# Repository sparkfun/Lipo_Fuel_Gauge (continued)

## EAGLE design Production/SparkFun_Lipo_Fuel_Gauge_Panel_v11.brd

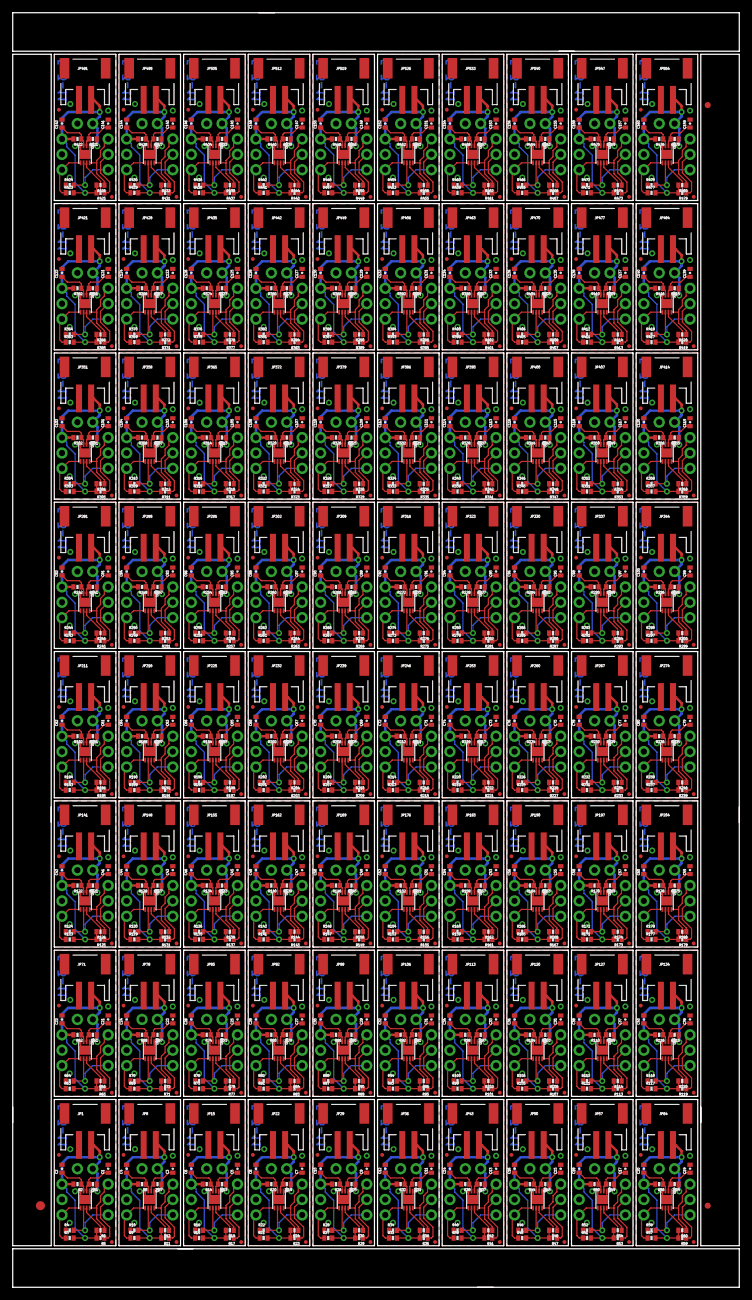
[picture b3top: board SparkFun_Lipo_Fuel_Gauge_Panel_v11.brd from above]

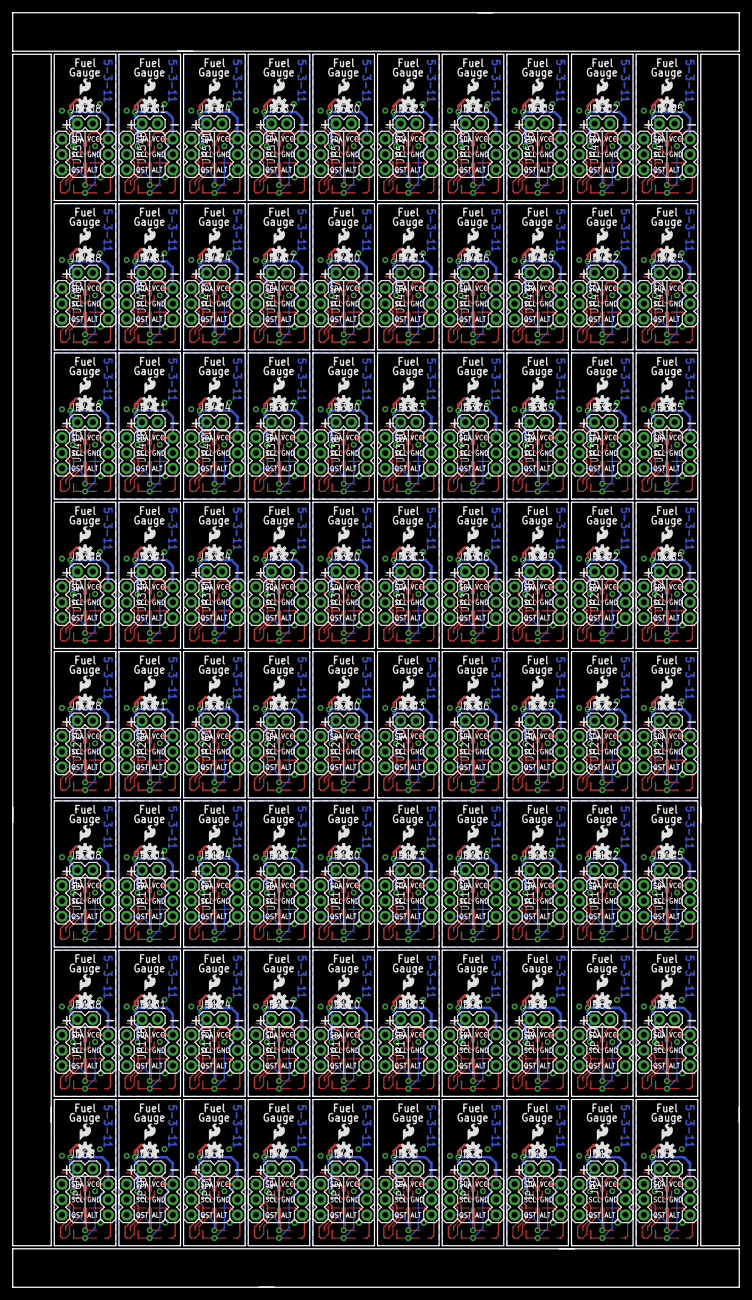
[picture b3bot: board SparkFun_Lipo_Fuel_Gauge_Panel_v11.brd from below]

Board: 2 copper layers, 119.9 x 210.3 mm, 1363 parts (400 on the bottom side), 640 nets.

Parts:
C1, C3, C5, C7, C9, C11, C13, C15, C17, C19, C21, C23, C25, C27, C29, C31, C33, C35, C37, C39, C41, C43, C45, C47, C49, C51, C53, C55, C57, C59, C61, C63, C65, C67, C69, C71, C73, C75, C77, C79, C81, C83, C85, C87, C89, C91, C93, C95, C97, C99, C101, C103, C105, C107, C109, C111, C113, C115, C117, C119, C121, C123, C125, C127, C129, C131, C133, C135, C137, C139, C141, C143, C145, C147, C149, C151, C153, C155, C157, C159: 1uF; 0402-CAP
C2, C4, C6, C8, C10, C12, C14, C16, C18, C20, C22, C24, C26, C28, C30, C32, C34, C36, C38, C40, C42, C44, C46, C48, C50, C52, C54, C56, C58, C60, C62, C64, C66, C68, C70, C72, C74, C76, C78, C80, C82, C84, C86, C88, C90, C92, C94, C96, C98, C100, C102, C104, C106, C108, C110, C112, C114, C116, C118, C120, C122, C124, C126, C128, C130, C132, C134, C136, C138, C140, C142, C144, C146, C148, C150, C152, C154, C156, C158, C160: 10nF; 0402-CAP
E$1: FIDUCIAL-1.5X3
E$2, E$5: FIDUCIAL-1X2
JP1, JP8, JP15, JP22, JP29, JP36, JP43, JP50, JP57, JP64, JP71, JP78, JP85, JP92, JP99, JP106, JP113, JP120, JP127, JP134, JP141, JP148, JP155, JP162, JP169, JP176, JP183, JP190, JP197, JP204, JP211, JP218, JP225, JP232, JP239, JP246, JP253, JP260, JP267, JP274, JP281, JP288, JP295, JP302, JP309, JP316, JP323, JP330, JP337, JP344, JP351, JP358, JP365, JP372, JP379, JP386, JP393, JP400, JP407, JP414, JP421, JP428, JP435, JP442, JP449, JP456, JP463, JP470, JP477, JP484, JP491, JP498, JP505, JP512, JP519, JP526, JP533, JP540, JP547, JP554: input; JST-2-SMD
JP2, JP4, JP9, JP10, JP16, JP17, JP23, JP24, JP30, JP31, JP37, JP38, JP44, JP45, JP51, JP52, JP58, JP59, JP65, JP66, JP72, JP73, JP79, JP80, JP86, JP87, JP93, JP94, JP100, JP101, JP107, JP108, JP114, JP115, JP121, JP122, JP128, JP129, JP135, JP136, JP142, JP143, JP149, JP150, JP156, JP157, JP163, JP164, JP170, JP171, JP177, JP178, JP184, JP185, JP191, JP192, JP198, JP199, JP205, JP206, JP212, JP213, JP219, JP220, JP226, JP227, JP233, JP234, JP240, JP241, JP247, JP248, JP254, JP255, JP261, JP262, JP268, JP269, JP275, JP276, JP282, JP283, JP289, JP290, JP296, JP297, JP303, JP304, JP310, JP311, JP317, JP318, JP324, JP325, JP331, JP332, JP338, JP339, JP345, JP346, JP352, JP353, JP359, JP360, JP366, JP367, JP373, JP374, JP380, JP381, JP387, JP388, JP394, JP395, JP401, JP402, JP408, JP409, JP415, JP416, JP422, JP423, JP429, JP430, JP436, JP437, JP443, JP444, JP450, JP451, JP457, JP458, JP464, JP465, JP471, JP472, JP478, JP479, JP485, JP486, JP492, JP493, JP499, JP500, JP506, JP507, JP513, JP514, JP520, JP521, JP527, JP528, JP534, JP535, JP541, JP542, JP548, JP549, JP555, JP556: 1X03
JP3, JP11, JP18, JP25, JP32, JP39, JP46, JP53, JP60, JP67, JP74, JP81, JP88, JP95, JP102, JP109, JP116, JP123, JP130, JP137, JP144, JP151, JP158, JP165, JP172, JP179, JP186, JP193, JP200, JP207, JP214, JP221, JP228, JP235, JP242, JP249, JP256, JP263, JP270, JP277, JP284, JP291, JP298, JP305, JP312, JP319, JP326, JP333, JP340, JP347, JP354, JP361, JP368, JP375, JP382, JP389, JP396, JP403, JP410, JP417, JP424, JP431, JP438, JP445, JP452, JP459, JP466, JP473, JP480, JP487, JP494, JP501, JP508, JP515, JP522, JP529, JP536, JP543, JP550, JP557: LOGO-SFESK; SFE-LOGO-FLAME
JP5, JP12, JP19, JP26, JP33, JP40, JP47, JP54, JP61, JP68, JP75, JP82, JP89, JP96, JP103, JP110, JP117, JP124, JP131, JP138, JP145, JP152, JP159, JP166, JP173, JP180, JP187, JP194, JP201, JP208, JP215, JP222, JP229, JP236, JP243, JP250, JP257, JP264, JP271, JP278, JP285, JP292, JP299, JP306, JP313, JP320, JP327, JP334, JP341, JP348, JP355, JP362, JP369, JP376, JP383, JP390, JP397, JP404, JP411, JP418, JP425, JP432, JP439, JP446, JP453, JP460, JP467, JP474, JP481, JP488, JP495, JP502, JP509, JP516, JP523, JP530, JP537, JP544, JP551, JP558: 1X02
JP6, JP7, JP13, JP14, JP20, JP21, JP27, JP28, JP34, JP35, JP41, JP42, JP48, JP49, JP55, JP56, JP62, JP63, JP69, JP70, JP76, JP77, JP83, JP84, JP90, JP91, JP97, JP98, JP104, JP105, JP111, JP112, JP118, JP119, JP125, JP126, JP132, JP133, JP139, JP140, JP146, JP147, JP153, JP154, JP160, JP161, JP167, JP168, JP174, JP175, JP181, JP182, JP188, JP189, JP195, JP196, JP202, JP203, JP209, JP210, JP216, JP217, JP223, JP224, JP230, JP231, JP237, JP238, JP244, JP245, JP251, JP252, JP258, JP259, JP265, JP266, JP272, JP273, JP279, JP280, JP286, JP287, JP293, JP294, JP300, JP301, JP307, JP308, JP314, JP315, JP321, JP322, JP328, JP329, JP335, JP336, JP342, JP343, JP349, JP350, JP356, JP357, JP363, JP364, JP370, JP371, JP377, JP378, JP384, JP385, JP391, JP392, JP398, JP399, JP405, JP406, JP412, JP413, JP419, JP420, JP426, JP427, JP433, JP434, JP440, JP441, JP447, JP448, JP454, JP455, JP461, JP462, JP468, JP469, JP475, JP476, JP482, JP483, JP489, JP490, JP496, JP497, JP503, JP504, JP510, JP511, JP517, JP518, JP524, JP525, JP531, JP532, JP538, JP539, JP545, JP546, JP552, JP553, JP559, JP560: FIDUCIAL1X2.5; FIDUCIAL-1X2.5
R1, R7, R13, R19, R25, R31, R37, R43, R49, R55, R61, R67, R73, R79, R85, R91, R97, R103, R109, R115, R121, R127, R133, R139, R145, R151, R157, R163, R169, R175, R181, R187, R193, R199, R205, R211, R217, R223, R229, R235, R241, R247, R253, R259, R265, R271, R277, R283, R289, R295, R301, R307, R313, R319, R325, R331, R337, R343, R349, R355, R361, R367, R373, R379, R385, R391, R397, R403, R409, R415, R421, R427, R433, R439, R445, R451, R457, R463, R469, R475: 1k; 0402-RES
R2, R8, R14, R20, R26, R32, R38, R44, R50, R56, R62, R68, R74, R80, R86, R92, R98, R104, R110, R116, R122, R128, R134, R140, R146, R152, R158, R164, R170, R176, R182, R188, R194, R200, R206, R212, R218, R224, R230, R236, R242, R248, R254, R260, R266, R272, R278, R284, R290, R296, R302, R308, R314, R320, R326, R332, R338, R344, R350, R356, R362, R368, R374, R380, R386, R392, R398, R404, R410, R416, R422, R428, R434, R440, R446, R452, R458, R464, R470, R476: 180; 0402-RES
R3, R4, R5, R6, R9, R10, R11, R12, R15, R16, R17, R18, R21, R22, R23, R24, R27, R28, R29, R30, R33, R34, R35, R36, R39, R40, R41, R42, R45, R46, R47, R48, R51, R52, R53, R54, R57, R58, R59, R60, R63, R64, R65, R66, R69, R70, R71, R72, R75, R76, R77, R78, R81, R82, R83, R84, R87, R88, R89, R90, R93, R94, R95, R96, R99, R100, R101, R102, R105, R106, R107, R108, R111, R112, R113, R114, R117, R118, R119, R120, R123, R124, R125, R126, R129, R130, R131, R132, R135, R136, R137, R138, R141, R142, R143, R144, R147, R148, R149, R150, R153, R154, R155, R156, R159, R160, R161, R162, R165, R166, R167, R168, R171, R172, R173, R174, R177, R178, R179, R180, R183, R184, R185, R186, R189, R190, R191, R192, R195, R196, R197, R198, R201, R202, R203, R204, R207, R208, R209, R210, R213, R214, R215, R216, R219, R220, R221, R222, R225, R226, R227, R228, R231, R232, R233, R234, R237, R238, R239, R240, R243, R244, R245, R246, R249, R250, R251, R252, R255, R256, R257, R258, R261, R262, R263, R264, R267, R268, R269, R270, R273, R274, R275, R276, R279, R280, R281, R282, R285, R286, R287, R288, R291, R292, R293, R294, R297, R298, R299, R300, R303, R304, R305, R306, R309, R310, R311, R312, R315, R316, R317, R318, R321, R322, R323, R324, R327, R328, R329, R330, R333, R334, R335, R336, R339, R340, R341, R342, R345, R346, R347, R348, R351, R352, R353, R354, R357, R358, R359, R360, R363, R364, R365, R366, R369, R370, R371, R372, R375, R376, R377, R378, R381, R382, R383, R384, R387, R388, R389, R390, R393, R394, R395, R396, R399, R400, R401, R402, R405, R406, R407, R408, R411, R412, R413, R414, R417, R418, R419, R420, R423, R424, R425, R426, R429, R430, R431, R432, R435, R436, R437, R438, R441, R442, R443, R444, R447, R448, R449, R450, R453, R454, R455, R456, R459, R460, R461, R462, R465, R466, R467, R468, R471, R472, R473, R474, R477, R478, R479, R480: 4.7k; 0402-RES
U1, U2, U3, U4, U5, U6, U7, U8, U9, U10, U11, U12, U13, U14, U15, U16, U17, U18, U19, U20, U21, U22, U23, U24, U25, U26, U27, U28, U29, U30, U31, U32, U33, U34, U35, U36, U37, U38, U39, U40, U41, U42, U43, U44, U45, U46, U47, U48, U49, U50, U51, U52, U53, U54, U55, U56, U57, U58, U59, U60, U61, U62, U63, U64, U65, U66, U67, U68, U69, U70, U71, U72, U73, U74, U75, U76, U77, U78, U79, U80: MAX1704X; TDFN-8
U$1, U$2, U$3, U$4, U$5, U$6, U$7, U$8, U$9, U$10, U$11, U$12, U$13, U$14, U$15, U$16, U$17, U$18, U$19, U$20, U$21, U$22, U$23, U$24, U$25, U$26, U$27, U$28, U$29, U$30, U$31, U$32, U$33, U$34, U$35, U$36, U$37, U$38, U$39, U$40, U$41, U$42, U$43, U$44, U$45, U$46, U$47, U$48, U$49, U$50, U$51, U$52, U$53, U$54, U$55, U$56, U$57, U$58, U$59, U$60, U$61, U$62, U$63, U$64, U$65, U$66, U$67, U$68, U$69, U$70, U$71, U$72, U$73, U$74, U$75, U$76, U$77, U$78, U$79, U$80: OSHW-LOGOS; OSHW-LOGO-S

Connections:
ALT: JP4.3, R3.1, U2.5
ALT1: JP10.3, R9.1, U1.5
ALT2: JP17.3, R15.1, U3.5
ALT3: JP24.3, R21.1, U4.5
ALT4: JP31.3, R27.1, U5.5
ALT5: JP38.3, R33.1, U6.5
ALT6: JP45.3, R39.1, U7.5
ALT7: JP52.3, R45.1, U8.5
ALT8: JP59.3, R51.1, U9.5
ALT9: JP66.3, R57.1, U10.5
ALT10: JP73.3, R63.1, U11.5
ALT11: JP80.3, R69.1, U12.5
ALT12: JP87.3, R75.1, U13.5
ALT13: JP94.3, R81.1, U14.5
ALT14: JP101.3, R87.1, U15.5
ALT15: JP108.3, R93.1, U16.5
ALT16: JP115.3, R99.1, U17.5
ALT17: JP122.3, R105.1, U18.5
ALT18: JP129.3, R111.1, U19.5
ALT19: JP136.3, R117.1, U20.5
ALT20: JP143.3, R123.1, U21.5
ALT21: JP150.3, R129.1, U22.5
ALT22: JP157.3, R135.1, U23.5
ALT23: JP164.3, R141.1, U24.5
ALT24: JP171.3, R147.1, U25.5
ALT25: JP178.3, R153.1, U26.5
ALT26: JP185.3, R159.1, U27.5
ALT27: JP192.3, R165.1, U28.5
ALT28: JP199.3, R171.1, U29.5
ALT29: JP206.3, R177.1, U30.5
ALT30: JP213.3, R183.1, U31.5
ALT31: JP220.3, R189.1, U32.5
ALT32: JP227.3, R195.1, U33.5
ALT33: JP234.3, R201.1, U34.5
ALT34: JP241.3, R207.1, U35.5
ALT35: JP248.3, R213.1, U36.5
ALT36: JP255.3, R219.1, U37.5
ALT37: JP262.3, R225.1, U38.5
ALT38: JP269.3, R231.1, U39.5
ALT39: JP276.3, R237.1, U40.5
ALT40: JP283.3, R243.1, U41.5
ALT41: JP290.3, R249.1, U42.5
ALT42: JP297.3, R255.1, U43.5
ALT43: JP304.3, R261.1, U44.5
ALT44: JP311.3, R267.1, U45.5
ALT45: JP318.3, R273.1, U46.5
ALT46: JP325.3, R279.1, U47.5
ALT47: JP332.3, R285.1, U48.5
ALT48: JP339.3, R291.1, U49.5
ALT49: JP346.3, R297.1, U50.5
ALT50: JP353.3, R303.1, U51.5
ALT51: JP360.3, R309.1, U52.5
ALT52: JP367.3, R315.1, U53.5
ALT53: JP374.3, R321.1, U54.5
ALT54: JP381.3, R327.1, U55.5
ALT55: JP388.3, R333.1, U56.5
ALT56: JP395.3, R339.1, U57.5
ALT57: JP402.3, R345.1, U58.5
ALT58: JP409.3, R351.1, U59.5
ALT59: JP416.3, R357.1, U60.5
ALT60: JP423.3, R363.1, U61.5
ALT61: JP430.3, R369.1, U62.5
ALT62: JP437.3, R375.1, U63.5
ALT63: JP444.3, R381.1, U64.5
ALT64: JP451.3, R387.1, U65.5
ALT65: JP458.3, R393.1, U66.5
ALT66: JP465.3, R399.1, U67.5
ALT67: JP472.3, R405.1, U68.5
ALT68: JP479.3, R411.1, U69.5
ALT69: JP486.3, R417.1, U70.5
ALT70: JP493.3, R423.1, U71.5
ALT71: JP500.3, R429.1, U72.5
ALT72: JP507.3, R435.1, U73.5
ALT73: JP514.3, R441.1, U74.5
ALT74: JP521.3, R447.1, U75.5
ALT75: JP528.3, R453.1, U76.5
ALT76: JP535.3, R459.1, U77.5
ALT77: JP542.3, R465.1, U78.5
ALT78: JP549.3, R471.1, U79.5
ALT79: JP556.3, R477.1, U80.5
GND: C1.2, C2.2, JP1.1, JP4.2, JP5.2, R4.1, U2.1, U2.4, U2.EP
GND1: C3.2, C4.2, JP8.1, JP10.2, JP12.2, R10.1, U1.1, U1.4, U1.EP
GND2: C5.2, C6.2, JP15.1, JP17.2, JP19.2, R16.1, U3.1, U3.4, U3.EP
GND3: C7.2, C8.2, JP22.1, JP24.2, JP26.2, R22.1, U4.1, U4.4, U4.EP
GND4: C9.2, C10.2, JP29.1, JP31.2, JP33.2, R28.1, U5.1, U5.4, U5.EP
GND5: C11.2, C12.2, JP36.1, JP38.2, JP40.2, R34.1, U6.1, U6.4, U6.EP
GND6: C13.2, C14.2, JP43.1, JP45.2, JP47.2, R40.1, U7.1, U7.4, U7.EP
GND7: C15.2, C16.2, JP50.1, JP52.2, JP54.2, R46.1, U8.1, U8.4, U8.EP
GND8: C17.2, C18.2, JP57.1, JP59.2, JP61.2, R52.1, U9.1, U9.4, U9.EP
GND9: C19.2, C20.2, JP64.1, JP66.2, JP68.2, R58.1, U10.1, U10.4, U10.EP
GND10: C21.2, C22.2, JP71.1, JP73.2, JP75.2, R64.1, U11.1, U11.4, U11.EP
GND11: C23.2, C24.2, JP78.1, JP80.2, JP82.2, R70.1, U12.1, U12.4, U12.EP
GND12: C25.2, C26.2, JP85.1, JP87.2, JP89.2, R76.1, U13.1, U13.4, U13.EP
GND13: C27.2, C28.2, JP92.1, JP94.2, JP96.2, R82.1, U14.1, U14.4, U14.EP
GND14: C29.2, C30.2, JP99.1, JP101.2, JP103.2, R88.1, U15.1, U15.4, U15.EP
GND15: C31.2, C32.2, JP106.1, JP108.2, JP110.2, R94.1, U16.1, U16.4, U16.EP
GND16: C33.2, C34.2, JP113.1, JP115.2, JP117.2, R100.1, U17.1, U17.4, U17.EP
GND17: C35.2, C36.2, JP120.1, JP122.2, JP124.2, R106.1, U18.1, U18.4, U18.EP
GND18: C37.2, C38.2, JP127.1, JP129.2, JP131.2, R112.1, U19.1, U19.4, U19.EP
GND19: C39.2, C40.2, JP134.1, JP136.2, JP138.2, R118.1, U20.1, U20.4, U20.EP
GND20: C41.2, C42.2, JP141.1, JP143.2, JP145.2, R124.1, U21.1, U21.4, U21.EP
GND21: C43.2, C44.2, JP148.1, JP150.2, JP152.2, R130.1, U22.1, U22.4, U22.EP
GND22: C45.2, C46.2, JP155.1, JP157.2, JP159.2, R136.1, U23.1, U23.4, U23.EP
GND23: C47.2, C48.2, JP162.1, JP164.2, JP166.2, R142.1, U24.1, U24.4, U24.EP
GND24: C49.2, C50.2, JP169.1, JP171.2, JP173.2, R148.1, U25.1, U25.4, U25.EP
GND25: C51.2, C52.2, JP176.1, JP178.2, JP180.2, R154.1, U26.1, U26.4, U26.EP
GND26: C53.2, C54.2, JP183.1, JP185.2, JP187.2, R160.1, U27.1, U27.4, U27.EP
GND27: C55.2, C56.2, JP190.1, JP192.2, JP194.2, R166.1, U28.1, U28.4, U28.EP
GND28: C57.2, C58.2, JP197.1, JP199.2, JP201.2, R172.1, U29.1, U29.4, U29.EP
GND29: C59.2, C60.2, JP204.1, JP206.2, JP208.2, R178.1, U30.1, U30.4, U30.EP
GND30: C61.2, C62.2, JP211.1, JP213.2, JP215.2, R184.1, U31.1, U31.4, U31.EP
GND31: C63.2, C64.2, JP218.1, JP220.2, JP222.2, R190.1, U32.1, U32.4, U32.EP
GND32: C65.2, C66.2, JP225.1, JP227.2, JP229.2, R196.1, U33.1, U33.4, U33.EP
GND33: C67.2, C68.2, JP232.1, JP234.2, JP236.2, R202.1, U34.1, U34.4, U34.EP
GND34: C69.2, C70.2, JP239.1, JP241.2, JP243.2, R208.1, U35.1, U35.4, U35.EP
GND35: C71.2, C72.2, JP246.1, JP248.2, JP250.2, R214.1, U36.1, U36.4, U36.EP
GND36: C73.2, C74.2, JP253.1, JP255.2, JP257.2, R220.1, U37.1, U37.4, U37.EP
GND37: C75.2, C76.2, JP260.1, JP262.2, JP264.2, R226.1, U38.1, U38.4, U38.EP
GND38: C77.2, C78.2, JP267.1, JP269.2, JP271.2, R232.1, U39.1, U39.4, U39.EP
GND39: C79.2, C80.2, JP274.1, JP276.2, JP278.2, R238.1, U40.1, U40.4, U40.EP
GND40: C81.2, C82.2, JP281.1, JP283.2, JP285.2, R244.1, U41.1, U41.4, U41.EP
GND41: C83.2, C84.2, JP288.1, JP290.2, JP292.2, R250.1, U42.1, U42.4, U42.EP
GND42: C85.2, C86.2, JP295.1, JP297.2, JP299.2, R256.1, U43.1, U43.4, U43.EP
GND43: C87.2, C88.2, JP302.1, JP304.2, JP306.2, R262.1, U44.1, U44.4, U44.EP
GND44: C89.2, C90.2, JP309.1, JP311.2, JP313.2, R268.1, U45.1, U45.4, U45.EP
GND45: C91.2, C92.2, JP316.1, JP318.2, JP320.2, R274.1, U46.1, U46.4, U46.EP
GND46: C93.2, C94.2, JP323.1, JP325.2, JP327.2, R280.1, U47.1, U47.4, U47.EP
GND47: C95.2, C96.2, JP330.1, JP332.2, JP334.2, R286.1, U48.1, U48.4, U48.EP
GND48: C97.2, C98.2, JP337.1, JP339.2, JP341.2, R292.1, U49.1, U49.4, U49.EP
GND49: C99.2, C100.2, JP344.1, JP346.2, JP348.2, R298.1, U50.1, U50.4, U50.EP
GND50: C101.2, C102.2, JP351.1, JP353.2, JP355.2, R304.1, U51.1, U51.4, U51.EP
GND51: C103.2, C104.2, JP358.1, JP360.2, JP362.2, R310.1, U52.1, U52.4, U52.EP
GND52: C105.2, C106.2, JP365.1, JP367.2, JP369.2, R316.1, U53.1, U53.4, U53.EP
GND53: C107.2, C108.2, JP372.1, JP374.2, JP376.2, R322.1, U54.1, U54.4, U54.EP
GND54: C109.2, C110.2, JP379.1, JP381.2, JP383.2, R328.1, U55.1, U55.4, U55.EP
GND55: C111.2, C112.2, JP386.1, JP388.2, JP390.2, R334.1, U56.1, U56.4, U56.EP
GND56: C113.2, C114.2, JP393.1, JP395.2, JP397.2, R340.1, U57.1, U57.4, U57.EP
GND57: C115.2, C116.2, JP400.1, JP402.2, JP404.2, R346.1, U58.1, U58.4, U58.EP
GND58: C117.2, C118.2, JP407.1, JP409.2, JP411.2, R352.1, U59.1, U59.4, U59.EP
GND59: C119.2, C120.2, JP414.1, JP416.2, JP418.2, R358.1, U60.1, U60.4, U60.EP
GND60: C121.2, C122.2, JP421.1, JP423.2, JP425.2, R364.1, U61.1, U61.4, U61.EP
GND61: C123.2, C124.2, JP428.1, JP430.2, JP432.2, R370.1, U62.1, U62.4, U62.EP
GND62: C125.2, C126.2, JP435.1, JP437.2, JP439.2, R376.1, U63.1, U63.4, U63.EP
GND63: C127.2, C128.2, JP442.1, JP444.2, JP446.2, R382.1, U64.1, U64.4, U64.EP
GND64: C129.2, C130.2, JP449.1, JP451.2, JP453.2, R388.1, U65.1, U65.4, U65.EP
GND65: C131.2, C132.2, JP456.1, JP458.2, JP460.2, R394.1, U66.1, U66.4, U66.EP
GND66: C133.2, C134.2, JP463.1, JP465.2, JP467.2, R400.1, U67.1, U67.4, U67.EP
GND67: C135.2, C136.2, JP470.1, JP472.2, JP474.2, R406.1, U68.1, U68.4, U68.EP
GND68: C137.2, C138.2, JP477.1, JP479.2, JP481.2, R412.1, U69.1, U69.4, U69.EP
GND69: C139.2, C140.2, JP484.1, JP486.2, JP488.2, R418.1, U70.1, U70.4, U70.EP
GND70: C141.2, C142.2, JP491.1, JP493.2, JP495.2, R424.1, U71.1, U71.4, U71.EP
GND71: C143.2, C144.2, JP498.1, JP500.2, JP502.2, R430.1, U72.1, U72.4, U72.EP
GND72: C145.2, C146.2, JP505.1, JP507.2, JP509.2, R436.1, U73.1, U73.4, U73.EP
GND73: C147.2, C148.2, JP512.1, JP514.2, JP516.2, R442.1, U74.1, U74.4, U74.EP
GND74: C149.2, C150.2, JP519.1, JP521.2, JP523.2, R448.1, U75.1, U75.4, U75.EP
GND75: C151.2, C152.2, JP526.1, JP528.2, JP530.2, R454.1, U76.1, U76.4, U76.EP
GND76: C153.2, C154.2, JP533.1, JP535.2, JP537.2, R460.1, U77.1, U77.4, U77.EP
GND77: C155.2, C156.2, JP540.1, JP542.2, JP544.2, R466.1, U78.1, U78.4, U78.EP
GND78: C157.2, C158.2, JP547.1, JP549.2, JP551.2, R472.1, U79.1, U79.4, U79.EP
GND79: C159.2, C160.2, JP554.1, JP556.2, JP558.2, R478.1, U80.1, U80.4, U80.EP
unnamed: C3.1, R7.2, U1.2
unnamed: C1.1, R1.2, U2.2
unnamed: C5.1, R13.2, U3.2
unnamed: C7.1, R19.2, U4.2
unnamed: C9.1, R25.2, U5.2
unnamed: C11.1, R31.2, U6.2
unnamed: C13.1, R37.2, U7.2
unnamed: C15.1, R43.2, U8.2
unnamed: C17.1, R49.2, U9.2
unnamed: C19.1, R55.2, U10.2
unnamed: C21.1, R61.2, U11.2
unnamed: C23.1, R67.2, U12.2
unnamed: C25.1, R73.2, U13.2
unnamed: C27.1, R79.2, U14.2
unnamed: C29.1, R85.2, U15.2
unnamed: C31.1, R91.2, U16.2
unnamed: C33.1, R97.2, U17.2
unnamed: C35.1, R103.2, U18.2
unnamed: C37.1, R109.2, U19.2
unnamed: C39.1, R115.2, U20.2
unnamed: C41.1, R121.2, U21.2
unnamed: C43.1, R127.2, U22.2
unnamed: C45.1, R133.2, U23.2
unnamed: C47.1, R139.2, U24.2
unnamed: C49.1, R145.2, U25.2
unnamed: C51.1, R151.2, U26.2
unnamed: C53.1, R157.2, U27.2
unnamed: C55.1, R163.2, U28.2
unnamed: C57.1, R169.2, U29.2
unnamed: C59.1, R175.2, U30.2
unnamed: C61.1, R181.2, U31.2
unnamed: C63.1, R187.2, U32.2
unnamed: C65.1, R193.2, U33.2
unnamed: C67.1, R199.2, U34.2
unnamed: C69.1, R205.2, U35.2
unnamed: C71.1, R211.2, U36.2
unnamed: C73.1, R217.2, U37.2
unnamed: C75.1, R223.2, U38.2
unnamed: C77.1, R229.2, U39.2
unnamed: C79.1, R235.2, U40.2
unnamed: C81.1, R241.2, U41.2
unnamed: C83.1, R247.2, U42.2
unnamed: C85.1, R253.2, U43.2
unnamed: C87.1, R259.2, U44.2
unnamed: C89.1, R265.2, U45.2
unnamed: C91.1, R271.2, U46.2
unnamed: C93.1, R277.2, U47.2
unnamed: C95.1, R283.2, U48.2
unnamed: C97.1, R289.2, U49.2
unnamed: C99.1, R295.2, U50.2
unnamed: C101.1, R301.2, U51.2
unnamed: C103.1, R307.2, U52.2
unnamed: C105.1, R313.2, U53.2
unnamed: C107.1, R319.2, U54.2
unnamed: C109.1, R325.2, U55.2
unnamed: C111.1, R331.2, U56.2
unnamed: C113.1, R337.2, U57.2
unnamed: C115.1, R343.2, U58.2
unnamed: C117.1, R349.2, U59.2
unnamed: C119.1, R355.2, U60.2
unnamed: C121.1, R361.2, U61.2
unnamed: C123.1, R367.2, U62.2
unnamed: C125.1, R373.2, U63.2
unnamed: C127.1, R379.2, U64.2
unnamed: C129.1, R385.2, U65.2
unnamed: C131.1, R391.2, U66.2
unnamed: C133.1, R397.2, U67.2
unnamed: C135.1, R403.2, U68.2
unnamed: C137.1, R409.2, U69.2
unnamed: C139.1, R415.2, U70.2
unnamed: C141.1, R421.2, U71.2
unnamed: C143.1, R427.2, U72.2
unnamed: C145.1, R433.2, U73.2
unnamed: C147.1, R439.2, U74.2
unnamed: C149.1, R445.2, U75.2
unnamed: C151.1, R451.2, U76.2
unnamed: C153.1, R457.2, U77.2
unnamed: C155.1, R463.2, U78.2
unnamed: C157.1, R469.2, U79.2
unnamed: C159.1, R475.2, U80.2
QST: JP2.3, R4.2, U2.6
QST1: JP9.3, R10.2, U1.6
QST2: JP16.3, R16.2, U3.6
QST3: JP23.3, R22.2, U4.6
QST4: JP30.3, R28.2, U5.6
QST5: JP37.3, R34.2, U6.6
QST6: JP44.3, R40.2, U7.6
QST7: JP51.3, R46.2, U8.6
QST8: JP58.3, R52.2, U9.6
QST9: JP65.3, R58.2, U10.6
QST10: JP72.3, R64.2, U11.6
QST11: JP79.3, R70.2, U12.6
QST12: JP86.3, R76.2, U13.6
QST13: JP93.3, R82.2, U14.6
QST14: JP100.3, R88.2, U15.6
QST15: JP107.3, R94.2, U16.6
QST16: JP114.3, R100.2, U17.6
QST17: JP121.3, R106.2, U18.6
QST18: JP128.3, R112.2, U19.6
QST19: JP135.3, R118.2, U20.6
QST20: JP142.3, R124.2, U21.6
QST21: JP149.3, R130.2, U22.6
QST22: JP156.3, R136.2, U23.6
QST23: JP163.3, R142.2, U24.6
QST24: JP170.3, R148.2, U25.6
QST25: JP177.3, R154.2, U26.6
QST26: JP184.3, R160.2, U27.6
QST27: JP191.3, R166.2, U28.6
QST28: JP198.3, R172.2, U29.6
QST29: JP205.3, R178.2, U30.6
QST30: JP212.3, R184.2, U31.6
QST31: JP219.3, R190.2, U32.6
QST32: JP226.3, R196.2, U33.6
QST33: JP233.3, R202.2, U34.6
QST34: JP240.3, R208.2, U35.6
QST35: JP247.3, R214.2, U36.6
QST36: JP254.3, R220.2, U37.6
QST37: JP261.3, R226.2, U38.6
QST38: JP268.3, R232.2, U39.6
QST39: JP275.3, R238.2, U40.6
QST40: JP282.3, R244.2, U41.6
QST41: JP289.3, R250.2, U42.6
QST42: JP296.3, R256.2, U43.6
QST43: JP303.3, R262.2, U44.6
QST44: JP310.3, R268.2, U45.6
QST45: JP317.3, R274.2, U46.6
QST46: JP324.3, R280.2, U47.6
QST47: JP331.3, R286.2, U48.6
QST48: JP338.3, R292.2, U49.6
QST49: JP345.3, R298.2, U50.6
QST50: JP352.3, R304.2, U51.6
QST51: JP359.3, R310.2, U52.6
QST52: JP366.3, R316.2, U53.6
QST53: JP373.3, R322.2, U54.6
QST54: JP380.3, R328.2, U55.6
QST55: JP387.3, R334.2, U56.6
QST56: JP394.3, R340.2, U57.6
QST57: JP401.3, R346.2, U58.6
QST58: JP408.3, R352.2, U59.6
QST59: JP415.3, R358.2, U60.6
QST60: JP422.3, R364.2, U61.6
QST61: JP429.3, R370.2, U62.6
QST62: JP436.3, R376.2, U63.6
QST63: JP443.3, R382.2, U64.6
QST64: JP450.3, R388.2, U65.6
QST65: JP457.3, R394.2, U66.6
QST66: JP464.3, R400.2, U67.6
QST67: JP471.3, R406.2, U68.6
QST68: JP478.3, R412.2, U69.6
QST69: JP485.3, R418.2, U70.6
QST70: JP492.3, R424.2, U71.6
QST71: JP499.3, R430.2, U72.6
QST72: JP506.3, R436.2, U73.6
QST73: JP513.3, R442.2, U74.6
QST74: JP520.3, R448.2, U75.6
QST75: JP527.3, R454.2, U76.6
QST76: JP534.3, R460.2, U77.6
QST77: JP541.3, R466.2, U78.6
QST78: JP548.3, R472.2, U79.6
QST79: JP555.3, R478.2, U80.6
SCL: JP2.2, R5.1, U2.7
SCL1: JP9.2, R11.1, U1.7
SCL2: JP16.2, R17.1, U3.7
SCL3: JP23.2, R23.1, U4.7
SCL4: JP30.2, R29.1, U5.7
SCL5: JP37.2, R35.1, U6.7
SCL6: JP44.2, R41.1, U7.7
SCL7: JP51.2, R47.1, U8.7
SCL8: JP58.2, R53.1, U9.7
SCL9: JP65.2, R59.1, U10.7
SCL10: JP72.2, R65.1, U11.7
SCL11: JP79.2, R71.1, U12.7
SCL12: JP86.2, R77.1, U13.7
SCL13: JP93.2, R83.1, U14.7
SCL14: JP100.2, R89.1, U15.7
SCL15: JP107.2, R95.1, U16.7
SCL16: JP114.2, R101.1, U17.7
SCL17: JP121.2, R107.1, U18.7
SCL18: JP128.2, R113.1, U19.7
SCL19: JP135.2, R119.1, U20.7
SCL20: JP142.2, R125.1, U21.7
SCL21: JP149.2, R131.1, U22.7
SCL22: JP156.2, R137.1, U23.7
SCL23: JP163.2, R143.1, U24.7
SCL24: JP170.2, R149.1, U25.7
SCL25: JP177.2, R155.1, U26.7
SCL26: JP184.2, R161.1, U27.7
SCL27: JP191.2, R167.1, U28.7
SCL28: JP198.2, R173.1, U29.7
SCL29: JP205.2, R179.1, U30.7
SCL30: JP212.2, R185.1, U31.7
SCL31: JP219.2, R191.1, U32.7
SCL32: JP226.2, R197.1, U33.7
SCL33: JP233.2, R203.1, U34.7
SCL34: JP240.2, R209.1, U35.7
SCL35: JP247.2, R215.1, U36.7
SCL36: JP254.2, R221.1, U37.7
SCL37: JP261.2, R227.1, U38.7
SCL38: JP268.2, R233.1, U39.7
SCL39: JP275.2, R239.1, U40.7
SCL40: JP282.2, R245.1, U41.7
SCL41: JP289.2, R251.1, U42.7
SCL42: JP296.2, R257.1, U43.7
SCL43: JP303.2, R263.1, U44.7
SCL44: JP310.2, R269.1, U45.7
SCL45: JP317.2, R275.1, U46.7
SCL46: JP324.2, R281.1, U47.7
SCL47: JP331.2, R287.1, U48.7
SCL48: JP338.2, R293.1, U49.7
SCL49: JP345.2, R299.1, U50.7
SCL50: JP352.2, R305.1, U51.7
SCL51: JP359.2, R311.1, U52.7
SCL52: JP366.2, R317.1, U53.7
SCL53: JP373.2, R323.1, U54.7
SCL54: JP380.2, R329.1, U55.7
SCL55: JP387.2, R335.1, U56.7
SCL56: JP394.2, R341.1, U57.7
SCL57: JP401.2, R347.1, U58.7
SCL58: JP408.2, R353.1, U59.7
SCL59: JP415.2, R359.1, U60.7
SCL60: JP422.2, R365.1, U61.7
SCL61: JP429.2, R371.1, U62.7
SCL62: JP436.2, R377.1, U63.7
SCL63: JP443.2, R383.1, U64.7
SCL64: JP450.2, R389.1, U65.7
SCL65: JP457.2, R395.1, U66.7
SCL66: JP464.2, R401.1, U67.7
SCL67: JP471.2, R407.1, U68.7
SCL68: JP478.2, R413.1, U69.7
SCL69: JP485.2, R419.1, U70.7
SCL70: JP492.2, R425.1, U71.7
SCL71: JP499.2, R431.1, U72.7
SCL72: JP506.2, R437.1, U73.7
SCL73: JP513.2, R443.1, U74.7
SCL74: JP520.2, R449.1, U75.7
SCL75: JP527.2, R455.1, U76.7
SCL76: JP534.2, R461.1, U77.7
SCL77: JP541.2, R467.1, U78.7
SCL78: JP548.2, R473.1, U79.7
SCL79: JP555.2, R479.1, U80.7
SDA: JP2.1, R6.1, U2.8
SDA1: JP9.1, R12.1, U1.8
SDA2: JP16.1, R18.1, U3.8
SDA3: JP23.1, R24.1, U4.8
SDA4: JP30.1, R30.1, U5.8
SDA5: JP37.1, R36.1, U6.8
SDA6: JP44.1, R42.1, U7.8
SDA7: JP51.1, R48.1, U8.8
SDA8: JP58.1, R54.1, U9.8
SDA9: JP65.1, R60.1, U10.8
SDA10: JP72.1, R66.1, U11.8
SDA11: JP79.1, R72.1, U12.8
SDA12: JP86.1, R78.1, U13.8
SDA13: JP93.1, R84.1, U14.8
SDA14: JP100.1, R90.1, U15.8
SDA15: JP107.1, R96.1, U16.8
SDA16: JP114.1, R102.1, U17.8
SDA17: JP121.1, R108.1, U18.8
SDA18: JP128.1, R114.1, U19.8
SDA19: JP135.1, R120.1, U20.8
SDA20: JP142.1, R126.1, U21.8
SDA21: JP149.1, R132.1, U22.8
SDA22: JP156.1, R138.1, U23.8
SDA23: JP163.1, R144.1, U24.8
SDA24: JP170.1, R150.1, U25.8
SDA25: JP177.1, R156.1, U26.8
SDA26: JP184.1, R162.1, U27.8
SDA27: JP191.1, R168.1, U28.8
SDA28: JP198.1, R174.1, U29.8
SDA29: JP205.1, R180.1, U30.8
SDA30: JP212.1, R186.1, U31.8
SDA31: JP219.1, R192.1, U32.8
SDA32: JP226.1, R198.1, U33.8
SDA33: JP233.1, R204.1, U34.8
SDA34: JP240.1, R210.1, U35.8
SDA35: JP247.1, R216.1, U36.8
SDA36: JP254.1, R222.1, U37.8
SDA37: JP261.1, R228.1, U38.8
SDA38: JP268.1, R234.1, U39.8
SDA39: JP275.1, R240.1, U40.8
SDA40: JP282.1, R246.1, U41.8
SDA41: JP289.1, R252.1, U42.8
SDA42: JP296.1, R258.1, U43.8
SDA43: JP303.1, R264.1, U44.8
SDA44: JP310.1, R270.1, U45.8
SDA45: JP317.1, R276.1, U46.8
SDA46: JP324.1, R282.1, U47.8
SDA47: JP331.1, R288.1, U48.8
SDA48: JP338.1, R294.1, U49.8
SDA49: JP345.1, R300.1, U50.8
SDA50: JP352.1, R306.1, U51.8
SDA51: JP359.1, R312.1, U52.8
SDA52: JP366.1, R318.1, U53.8
SDA53: JP373.1, R324.1, U54.8
SDA54: JP380.1, R330.1, U55.8
SDA55: JP387.1, R336.1, U56.8
SDA56: JP394.1, R342.1, U57.8
SDA57: JP401.1, R348.1, U58.8
SDA58: JP408.1, R354.1, U59.8
SDA59: JP415.1, R360.1, U60.8
SDA60: JP422.1, R366.1, U61.8
SDA61: JP429.1, R372.1, U62.8
SDA62: JP436.1, R378.1, U63.8
SDA63: JP443.1, R384.1, U64.8
SDA64: JP450.1, R390.1, U65.8
SDA65: JP457.1, R396.1, U66.8
SDA66: JP464.1, R402.1, U67.8
SDA67: JP471.1, R408.1, U68.8
SDA68: JP478.1, R414.1, U69.8
SDA69: JP485.1, R420.1, U70.8
SDA70: JP492.1, R426.1, U71.8
SDA71: JP499.1, R432.1, U72.8
SDA72: JP506.1, R438.1, U73.8
SDA73: JP513.1, R444.1, U74.8
SDA74: JP520.1, R450.1, U75.8
SDA75: JP527.1, R456.1, U76.8
SDA76: JP534.1, R462.1, U77.8
SDA77: JP541.1, R468.1, U78.8
SDA78: JP548.1, R474.1, U79.8
SDA79: JP555.1, R480.1, U80.8
VCC: JP1.2, JP4.1, JP5.1, R1.1, R2.2, R3.2, R5.2, R6.2
VCC1: JP8.2, JP10.1, JP12.1, R7.1, R8.2, R9.2, R11.2, R12.2
VCC2: JP15.2, JP17.1, JP19.1, R13.1, R14.2, R15.2, R17.2, R18.2
VCC3: JP22.2, JP24.1, JP26.1, R19.1, R20.2, R21.2, R23.2, R24.2
VCC4: JP29.2, JP31.1, JP33.1, R25.1, R26.2, R27.2, R29.2, R30.2
VCC5: JP36.2, JP38.1, JP40.1, R31.1, R32.2, R33.2, R35.2, R36.2
VCC6: JP43.2, JP45.1, JP47.1, R37.1, R38.2, R39.2, R41.2, R42.2
VCC7: JP50.2, JP52.1, JP54.1, R43.1, R44.2, R45.2, R47.2, R48.2
VCC8: JP57.2, JP59.1, JP61.1, R49.1, R50.2, R51.2, R53.2, R54.2
VCC9: JP64.2, JP66.1, JP68.1, R55.1, R56.2, R57.2, R59.2, R60.2
VCC10: JP71.2, JP73.1, JP75.1, R61.1, R62.2, R63.2, R65.2, R66.2
VCC11: JP78.2, JP80.1, JP82.1, R67.1, R68.2, R69.2, R71.2, R72.2
VCC12: JP85.2, JP87.1, JP89.1, R73.1, R74.2, R75.2, R77.2, R78.2
VCC13: JP92.2, JP94.1, JP96.1, R79.1, R80.2, R81.2, R83.2, R84.2
VCC14: JP99.2, JP101.1, JP103.1, R85.1, R86.2, R87.2, R89.2, R90.2
VCC15: JP106.2, JP108.1, JP110.1, R91.1, R92.2, R93.2, R95.2, R96.2
VCC16: JP113.2, JP115.1, JP117.1, R97.1, R98.2, R99.2, R101.2, R102.2
VCC17: JP120.2, JP122.1, JP124.1, R103.1, R104.2, R105.2, R107.2, R108.2
VCC18: JP127.2, JP129.1, JP131.1, R109.1, R110.2, R111.2, R113.2, R114.2
VCC19: JP134.2, JP136.1, JP138.1, R115.1, R116.2, R117.2, R119.2, R120.2
VCC20: JP141.2, JP143.1, JP145.1, R121.1, R122.2, R123.2, R125.2, R126.2
VCC21: JP148.2, JP150.1, JP152.1, R127.1, R128.2, R129.2, R131.2, R132.2
VCC22: JP155.2, JP157.1, JP159.1, R133.1, R134.2, R135.2, R137.2, R138.2
VCC23: JP162.2, JP164.1, JP166.1, R139.1, R140.2, R141.2, R143.2, R144.2
VCC24: JP169.2, JP171.1, JP173.1, R145.1, R146.2, R147.2, R149.2, R150.2
VCC25: JP176.2, JP178.1, JP180.1, R151.1, R152.2, R153.2, R155.2, R156.2
VCC26: JP183.2, JP185.1, JP187.1, R157.1, R158.2, R159.2, R161.2, R162.2
VCC27: JP190.2, JP192.1, JP194.1, R163.1, R164.2, R165.2, R167.2, R168.2
VCC28: JP197.2, JP199.1, JP201.1, R169.1, R170.2, R171.2, R173.2, R174.2
VCC29: JP204.2, JP206.1, JP208.1, R175.1, R176.2, R177.2, R179.2, R180.2
VCC30: JP211.2, JP213.1, JP215.1, R181.1, R182.2, R183.2, R185.2, R186.2
VCC31: JP218.2, JP220.1, JP222.1, R187.1, R188.2, R189.2, R191.2, R192.2
VCC32: JP225.2, JP227.1, JP229.1, R193.1, R194.2, R195.2, R197.2, R198.2
VCC33: JP232.2, JP234.1, JP236.1, R199.1, R200.2, R201.2, R203.2, R204.2
VCC34: JP239.2, JP241.1, JP243.1, R205.1, R206.2, R207.2, R209.2, R210.2
VCC35: JP246.2, JP248.1, JP250.1, R211.1, R212.2, R213.2, R215.2, R216.2
VCC36: JP253.2, JP255.1, JP257.1, R217.1, R218.2, R219.2, R221.2, R222.2
VCC37: JP260.2, JP262.1, JP264.1, R223.1, R224.2, R225.2, R227.2, R228.2
VCC38: JP267.2, JP269.1, JP271.1, R229.1, R230.2, R231.2, R233.2, R234.2
VCC39: JP274.2, JP276.1, JP278.1, R235.1, R236.2, R237.2, R239.2, R240.2
VCC40: JP281.2, JP283.1, JP285.1, R241.1, R242.2, R243.2, R245.2, R246.2
VCC41: JP288.2, JP290.1, JP292.1, R247.1, R248.2, R249.2, R251.2, R252.2
VCC42: JP295.2, JP297.1, JP299.1, R253.1, R254.2, R255.2, R257.2, R258.2
VCC43: JP302.2, JP304.1, JP306.1, R259.1, R260.2, R261.2, R263.2, R264.2
VCC44: JP309.2, JP311.1, JP313.1, R265.1, R266.2, R267.2, R269.2, R270.2
VCC45: JP316.2, JP318.1, JP320.1, R271.1, R272.2, R273.2, R275.2, R276.2
VCC46: JP323.2, JP325.1, JP327.1, R277.1, R278.2, R279.2, R281.2, R282.2
VCC47: JP330.2, JP332.1, JP334.1, R283.1, R284.2, R285.2, R287.2, R288.2
VCC48: JP337.2, JP339.1, JP341.1, R289.1, R290.2, R291.2, R293.2, R294.2
VCC49: JP344.2, JP346.1, JP348.1, R295.1, R296.2, R297.2, R299.2, R300.2
VCC50: JP351.2, JP353.1, JP355.1, R301.1, R302.2, R303.2, R305.2, R306.2
VCC51: JP358.2, JP360.1, JP362.1, R307.1, R308.2, R309.2, R311.2, R312.2
VCC52: JP365.2, JP367.1, JP369.1, R313.1, R314.2, R315.2, R317.2, R318.2
VCC53: JP372.2, JP374.1, JP376.1, R319.1, R320.2, R321.2, R323.2, R324.2
VCC54: JP379.2, JP381.1, JP383.1, R325.1, R326.2, R327.2, R329.2, R330.2
VCC55: JP386.2, JP388.1, JP390.1, R331.1, R332.2, R333.2, R335.2, R336.2
VCC56: JP393.2, JP395.1, JP397.1, R337.1, R338.2, R339.2, R341.2, R342.2
VCC57: JP400.2, JP402.1, JP404.1, R343.1, R344.2, R345.2, R347.2, R348.2
VCC58: JP407.2, JP409.1, JP411.1, R349.1, R350.2, R351.2, R353.2, R354.2
VCC59: JP414.2, JP416.1, JP418.1, R355.1, R356.2, R357.2, R359.2, R360.2
VCC60: JP421.2, JP423.1, JP425.1, R361.1, R362.2, R363.2, R365.2, R366.2
VCC61: JP428.2, JP430.1, JP432.1, R367.1, R368.2, R369.2, R371.2, R372.2
VCC62: JP435.2, JP437.1, JP439.1, R373.1, R374.2, R375.2, R377.2, R378.2
VCC63: JP442.2, JP444.1, JP446.1, R379.1, R380.2, R381.2, R383.2, R384.2
VCC64: JP449.2, JP451.1, JP453.1, R385.1, R386.2, R387.2, R389.2, R390.2
VCC65: JP456.2, JP458.1, JP460.1, R391.1, R392.2, R393.2, R395.2, R396.2
VCC66: JP463.2, JP465.1, JP467.1, R397.1, R398.2, R399.2, R401.2, R402.2
VCC67: JP470.2, JP472.1, JP474.1, R403.1, R404.2, R405.2, R407.2, R408.2
VCC68: JP477.2, JP479.1, JP481.1, R409.1, R410.2, R411.2, R413.2, R414.2
VCC69: JP484.2, JP486.1, JP488.1, R415.1, R416.2, R417.2, R419.2, R420.2
VCC70: JP491.2, JP493.1, JP495.1, R421.1, R422.2, R423.2, R425.2, R426.2
VCC71: JP498.2, JP500.1, JP502.1, R427.1, R428.2, R429.2, R431.2, R432.2
VCC72: JP505.2, JP507.1, JP509.1, R433.1, R434.2, R435.2, R437.2, R438.2
VCC73: JP512.2, JP514.1, JP516.1, R439.1, R440.2, R441.2, R443.2, R444.2
VCC74: JP519.2, JP521.1, JP523.1, R445.1, R446.2, R447.2, R449.2, R450.2
VCC75: JP526.2, JP528.1, JP530.1, R451.1, R452.2, R453.2, R455.2, R456.2
VCC76: JP533.2, JP535.1, JP537.1, R457.1, R458.2, R459.2, R461.2, R462.2
VCC77: JP540.2, JP542.1, JP544.1, R463.1, R464.2, R465.2, R467.2, R468.2
VCC78: JP547.2, JP549.1, JP551.1, R469.1, R470.2, R471.2, R473.2, R474.2
VCC79: JP554.2, JP556.1, JP558.1, R475.1, R476.2, R477.2, R479.2, R480.2
VDD: C2.1, R2.1, U2.3
VDD1: C4.1, R8.1, U1.3
VDD2: C6.1, R14.1, U3.3
VDD3: C8.1, R20.1, U4.3
VDD4: C10.1, R26.1, U5.3
VDD5: C12.1, R32.1, U6.3
VDD6: C14.1, R38.1, U7.3
VDD7: C16.1, R44.1, U8.3
VDD8: C18.1, R50.1, U9.3
VDD9: C20.1, R56.1, U10.3
VDD10: C22.1, R62.1, U11.3
VDD11: C24.1, R68.1, U12.3
VDD12: C26.1, R74.1, U13.3
VDD13: C28.1, R80.1, U14.3
VDD14: C30.1, R86.1, U15.3
VDD15: C32.1, R92.1, U16.3
VDD16: C34.1, R98.1, U17.3
VDD17: C36.1, R104.1, U18.3
VDD18: C38.1, R110.1, U19.3
VDD19: C40.1, R116.1, U20.3
VDD20: C42.1, R122.1, U21.3
VDD21: C44.1, R128.1, U22.3
VDD22: C46.1, R134.1, U23.3
VDD23: C48.1, R140.1, U24.3
VDD24: C50.1, R146.1, U25.3
VDD25: C52.1, R152.1, U26.3
VDD26: C54.1, R158.1, U27.3
VDD27: C56.1, R164.1, U28.3
VDD28: C58.1, R170.1, U29.3
VDD29: C60.1, R176.1, U30.3
VDD30: C62.1, R182.1, U31.3
VDD31: C64.1, R188.1, U32.3
VDD32: C66.1, R194.1, U33.3
VDD33: C68.1, R200.1, U34.3
VDD34: C70.1, R206.1, U35.3
VDD35: C72.1, R212.1, U36.3
VDD36: C74.1, R218.1, U37.3
VDD37: C76.1, R224.1, U38.3
VDD38: C78.1, R230.1, U39.3
VDD39: C80.1, R236.1, U40.3
VDD40: C82.1, R242.1, U41.3
VDD41: C84.1, R248.1, U42.3
VDD42: C86.1, R254.1, U43.3
VDD43: C88.1, R260.1, U44.3
VDD44: C90.1, R266.1, U45.3
VDD45: C92.1, R272.1, U46.3
VDD46: C94.1, R278.1, U47.3
VDD47: C96.1, R284.1, U48.3
VDD48: C98.1, R290.1, U49.3
VDD49: C100.1, R296.1, U50.3
VDD50: C102.1, R302.1, U51.3
VDD51: C104.1, R308.1, U52.3
VDD52: C106.1, R314.1, U53.3
VDD53: C108.1, R320.1, U54.3
VDD54: C110.1, R326.1, U55.3
VDD55: C112.1, R332.1, U56.3
VDD56: C114.1, R338.1, U57.3
VDD57: C116.1, R344.1, U58.3
VDD58: C118.1, R350.1, U59.3
VDD59: C120.1, R356.1, U60.3
VDD60: C122.1, R362.1, U61.3
VDD61: C124.1, R368.1, U62.3
VDD62: C126.1, R374.1, U63.3
VDD63: C128.1, R380.1, U64.3
VDD64: C130.1, R386.1, U65.3
VDD65: C132.1, R392.1, U66.3
VDD66: C134.1, R398.1, U67.3
VDD67: C136.1, R404.1, U68.3
VDD68: C138.1, R410.1, U69.3
VDD69: C140.1, R416.1, U70.3
VDD70: C142.1, R422.1, U71.3
VDD71: C144.1, R428.1, U72.3
VDD72: C146.1, R434.1, U73.3
VDD73: C148.1, R440.1, U74.3
VDD74: C150.1, R446.1, U75.3
VDD75: C152.1, R452.1, U76.3
VDD76: C154.1, R458.1, U77.3
VDD77: C156.1, R464.1, U78.3
VDD78: C158.1, R470.1, U79.3
VDD79: C160.1, R476.1, U80.3

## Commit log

2015-05-06 Adding hardware files, readme, example code
2015-10-19 created panel v11
2022-07-20 Revision updates
    Purpose of revision:
    VCC connects directly to battery, which means a user could connect a 3V3 signal to 4V2 of the battery, causing things to break (see latest 1-star review on product page). This revision is to separate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
    Schematic changes:
    Add Revised By
    Update revision number
    Replace VCC on battery side with V_BATT symbol
2022-07-21 Design review updates
    Schematic:
    Replace old Eagle devices with current ones
    Update MAX1704X symbol to match current standards
    Add warning about single cell LiPo only
    Add voltage range for V_BATT and VCC
    Add I2C pullup isolation jumper
2022-07-22 Silk change
    Change Buzzard labels to non-pill style to fit larger text.
2022-07-22 Remove pad numbers from schematic
2022-08-02 Fix MAX1704X PROD_ID
2022-08-09 Update production files for v12
2023-02-27 Upload Combined Arduino Examples used in Tutorial
